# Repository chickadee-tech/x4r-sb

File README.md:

# Chickadee Tech X4R-SB Cradle Polystack Mod #
This mod cradles an X4R-SB to add it to the Polystack. It supports both the Serial RX and telemetry connections.

## Documentation ##
See the [wiki](https://github.com/chickadee-tech/x4r-sb/wiki) for documentation.

## Polystack ##
This **mod** board is part of the Polystack platform for modular microcontrol systems. More information on the platform can be found at [polystack.org](http://polystack.org).

## Support ##
If you need support with a board you own or have development questions please email support@chickadee.tech or check [chickadee.tech/support](https://chickadee.tech/support) for other ways to get support.

## Contributing ##
Please note that this project is released with a [Contributor Code of Conduct](CODE_OF_CONDUCT.md). By participating in this project you agree to abide by its terms.

### Setup ###
Components and footprints for PCB parts are not included in this repository. Instead, checkout the [chickadee-tech/kicad-libs](https://github.com/chickadee-tech/kicad-libs) repository in the same directory that this repository is checked out in. All part definitions should be relative so that they will load correctly.

### Pull requests ###
For fixes please submit a pull request to the original repository. After the pull request is merged, check the [Chickadee Tech Active Contributor Discount (ACD)](https://chickadee.tech/active-contributor) to see if you are eligible for a discount code to use on your next purchase.

### Derivatives ###
If developing your own version of the X4R-SB board please remove all Chickadee Tech trademarks and follow the [CC-BY license](LICENSE). While not required, please consider open sourcing your modifications so others can learn from your improvements. If you do email support@chickadee.tech and we may choose to add your project to the ACD.

You may also license the Polystack logo for free by emailing support@chickadee.tech. We'll ask for your gerbers to ensure the design complies with specifications laid out [here](https://github.com/chickadee-tech/polystack/wiki) and provide written permission to use the trademark after compliance has been demonstrated.

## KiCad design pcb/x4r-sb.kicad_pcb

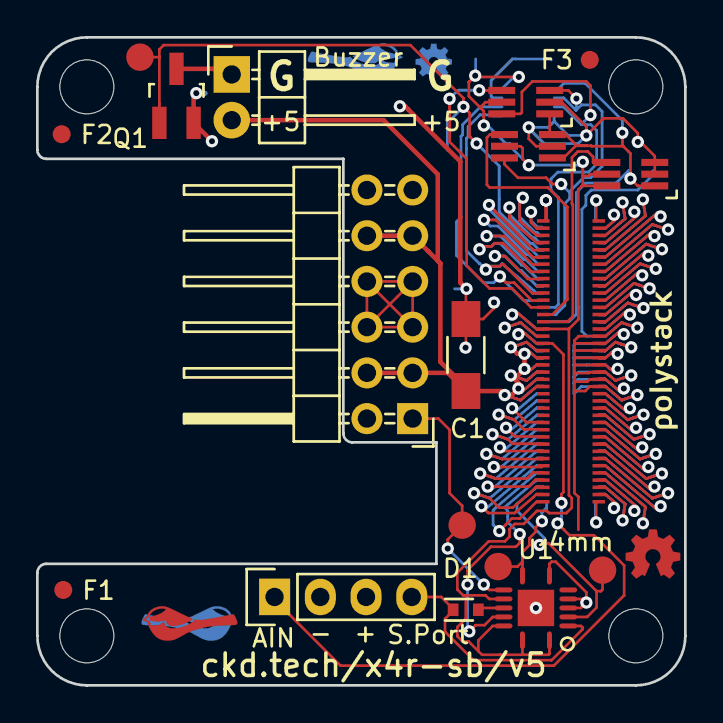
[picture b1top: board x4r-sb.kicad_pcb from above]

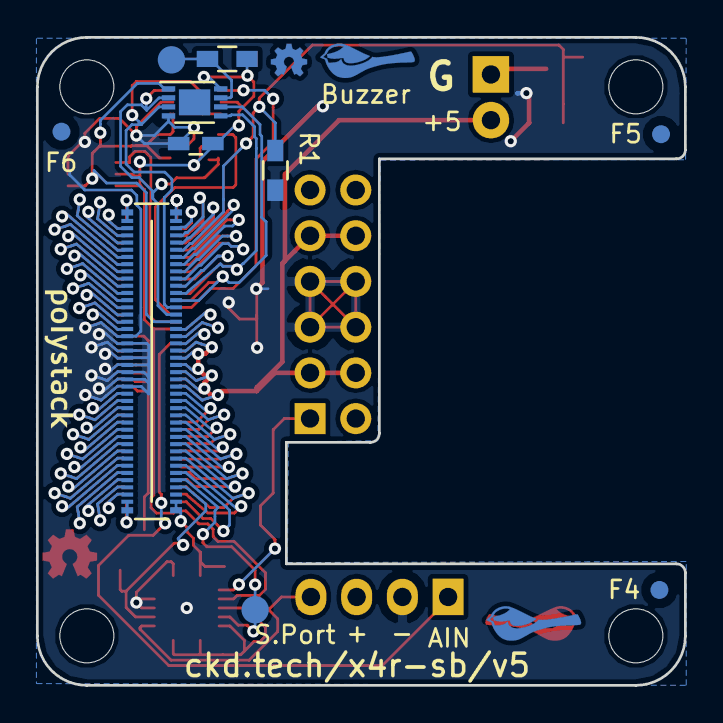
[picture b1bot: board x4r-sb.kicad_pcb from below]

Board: 2 copper layers, 36.0 x 36.0 mm, 30 parts (11 on the bottom side), 75 nets.

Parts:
C1: 10uF; C_1206_HandSoldering
D1: D_Schottky_Small; SOD-523
F1, F2, F3, F4, F5, F6: 1mm; Fiducial
P1: CONN_01X04; Pin_Header_Straight_1x04
P2: CONN_02X06; Pin_Header_Angled_2x06
P3: CONN_01X02; Pin_Header_Angled_1x02
P5, P7, P8, P9, P10: CONN_01X01; Measurement_Point_Round-SMD-Pad_Small
PORT_ANDOR1: SN74LVC1G0832; SC-70-6_Handsoldering
PORT_C1: 0.1uF; C_0603_HandSoldering
PORT_IC1: AT24CS02-MAHM; DFN-8-1EP_3x2mm_Pitch0.5mm
PORT_IN1: CKD_SANDWICH; DF40-80pin-Header
PORT_INV1: SN74LVC1G58; SC-70-6_Handsoldering
PORT_OUT1: CKD_SANDWICH; DF40-3-4mm-80pin-Receptacle
PORT_P1: CONN_01X01; Measurement_Point_Round-SMD-Pad_Small
PORT_R1: 10k; R_0603_HandSoldering
PORT_XOR1: SN74LVC1G58; SC-70-6_Handsoldering
Q1: Q_NMOS_GSD; SOT-23_Handsoldering
R1: 10k; R_0603_HandSoldering
U1: 74LS86; QFN-14-3.5x3.5mm
svg2mod, svg2mod#2: G***; polystack-bold-0.4

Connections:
+3V3: PORT_ANDOR1.5, PORT_C1.1, PORT_IC1.8, PORT_IN1.16, PORT_INV1.5, PORT_INV1.6, PORT_OUT1.16, PORT_R1.2, PORT_XOR1.5, U1.1, U1.10, U1.13, U1.14
+5V: C1.1, P2.3, P2.4, P2.9, P2.10, P3.2, PORT_IN1.19, PORT_IN1.20, PORT_IN1.21, PORT_IN1.22, PORT_IN1.23, PORT_IN1.24, PORT_OUT1.19, PORT_OUT1.20, PORT_OUT1.21, PORT_OUT1.22, PORT_OUT1.23, PORT_OUT1.24
/ExpansionPort/3V3_0.3A_E: PORT_IN1.17, PORT_OUT1.17
/ExpansionPort/ADC1: PORT_IN1.49, PORT_OUT1.49
/ExpansionPort/ADC2: PORT_IN1.50, PORT_OUT1.50
/ExpansionPort/BATT_DIV: P1.1, PORT_IN1.18, PORT_OUT1.18
/ExpansionPort/BOOT: PORT_IN1.65, PORT_OUT1.65
/ExpansionPort/CAN_HI: PORT_IN1.67, PORT_OUT1.67
/ExpansionPort/CAN_LO: PORT_IN1.68, PORT_OUT1.68
/ExpansionPort/GPIO1: P10.1, PORT_IN1.5, Q1.1, R1.1
/ExpansionPort/GPIO2: PORT_IN1.6, PORT_OUT1.5
/ExpansionPort/GPIO3: PORT_IN1.7, PORT_OUT1.6
/ExpansionPort/GPIO4: PORT_IN1.8, PORT_OUT1.7
/ExpansionPort/GPIO5: PORT_IN1.9, PORT_OUT1.8
/ExpansionPort/GPIO6: PORT_IN1.10, PORT_OUT1.9
/ExpansionPort/HEIGHT_1: PORT_ANDOR1.1, PORT_IC1.1, PORT_IN1.15, PORT_INV1.1, PORT_XOR1.1, PORT_XOR1.3
/ExpansionPort/HEIGHT_2: PORT_ANDOR1.3, PORT_IC1.2, PORT_IN1.14, PORT_XOR1.6
/ExpansionPort/HEIGHT_4: PORT_ANDOR1.6, PORT_IC1.3, PORT_IN1.13
/ExpansionPort/NEW_HEIGHT_1: PORT_INV1.4, PORT_OUT1.15
/ExpansionPort/NEW_HEIGHT_2: PORT_OUT1.14, PORT_XOR1.4
/ExpansionPort/NEW_HEIGHT_4: PORT_ANDOR1.4, PORT_OUT1.13
/ExpansionPort/RESET: PORT_IN1.66, PORT_OUT1.66
/ExpansionPort/SDMMC1_CK: PORT_IN1.55, PORT_OUT1.55
/ExpansionPort/SDMMC1_CMD: PORT_IN1.56, PORT_OUT1.56
/ExpansionPort/SDMMC1_D0: PORT_IN1.51, PORT_OUT1.51
/ExpansionPort/SDMMC1_D1: PORT_IN1.52, PORT_OUT1.52
/ExpansionPort/SDMMC1_D2: PORT_IN1.53, PORT_OUT1.53
/ExpansionPort/SDMMC1_D3: PORT_IN1.54, PORT_OUT1.54
/ExpansionPort/SPI1_MISO: PORT_IN1.79, PORT_OUT1.79
/ExpansionPort/SPI1_MOSI: PORT_IN1.80, PORT_OUT1.80
/ExpansionPort/SPI1_NSS: PORT_IN1.77, PORT_OUT1.77
/ExpansionPort/SPI1_SCK: PORT_IN1.78, PORT_OUT1.78
/ExpansionPort/SPI2_MISO: PORT_IN1.75, PORT_OUT1.75
/ExpansionPort/SPI2_MOSI: PORT_IN1.76, PORT_OUT1.76
/ExpansionPort/SPI2_NSS: PORT_IN1.73, PORT_OUT1.73
/ExpansionPort/SPI2_SCK: PORT_IN1.74, PORT_OUT1.74
/ExpansionPort/SPI3_MISO: PORT_IN1.71, PORT_OUT1.71
/ExpansionPort/SPI3_MOSI: PORT_IN1.72, PORT_OUT1.72
/ExpansionPort/SPI3_NSS: PORT_IN1.69, PORT_OUT1.69
/ExpansionPort/SPI3_SCK: PORT_IN1.70, PORT_OUT1.70
/ExpansionPort/TIM1: PORT_IN1.1, PORT_OUT1.1
/ExpansionPort/TIM2: PORT_IN1.2, PORT_OUT1.2
/ExpansionPort/TIM3: PORT_IN1.3, PORT_OUT1.3
/ExpansionPort/TIM4: PORT_IN1.4, PORT_OUT1.4
/ExpansionPort/TIMG1_CH1: PORT_IN1.41, PORT_OUT1.41
/ExpansionPort/TIMG1_CH2: PORT_IN1.42, PORT_OUT1.42
/ExpansionPort/TIMG1_CH3: PORT_IN1.43, PORT_OUT1.43
/ExpansionPort/TIMG1_CH4: PORT_IN1.44, PORT_OUT1.44
/ExpansionPort/TIMG2_CH1: PORT_IN1.45, PORT_OUT1.45
/ExpansionPort/TIMG2_CH2: PORT_IN1.46, PORT_OUT1.46
/ExpansionPort/TIMG2_CH3: PORT_IN1.47, PORT_OUT1.47
/ExpansionPort/TIMG2_CH4: PORT_IN1.48, PORT_OUT1.48
/ExpansionPort/UART1_RX: P7.1, PORT_IN1.40, U1.8
/ExpansionPort/UART2_RX: P8.1, PORT_IN1.38, U1.3
/ExpansionPort/UART2_TX: P9.1, PORT_IN1.37, U1.12
/ExpansionPort/UART3_RX: PORT_IN1.36, PORT_OUT1.40
/ExpansionPort/UART3_TX: PORT_IN1.35, PORT_OUT1.39
/ExpansionPort/UART4_RX: PORT_IN1.34, PORT_OUT1.38
/ExpansionPort/UART4_TX: PORT_IN1.33, PORT_OUT1.37
/ExpansionPort/UART5_RX: PORT_IN1.32, PORT_OUT1.36
/ExpansionPort/UART5_TX: PORT_IN1.31, PORT_OUT1.35
/ExpansionPort/UART6_RX: PORT_IN1.30, PORT_OUT1.34
/ExpansionPort/UART6_TX: PORT_IN1.29, PORT_OUT1.33
/ExpansionPort/UART7_RX: PORT_IN1.28, PORT_OUT1.32
/ExpansionPort/UART7_TX: PORT_IN1.27, PORT_OUT1.31
/ExpansionPort/UART8_RX: PORT_IN1.26, PORT_OUT1.30
/ExpansionPort/UART8_TX: PORT_IN1.25, PORT_OUT1.29
/ExpansionPort/i2c_SCL: PORT_IC1.6, PORT_IN1.12, PORT_OUT1.12
/ExpansionPort/i2c_SDA: PORT_IC1.5, PORT_IN1.11, PORT_OUT1.11
/S.Port: D1.1, P1.4, U1.2
/nRC_RX: P2.1, P5.1, U1.9
GND: C1.2, P1.2, P2.5, P2.6, P2.7, P2.8, PORT_ANDOR1.2, PORT_C1.2, PORT_IC1.4, PORT_IN1.57, PORT_IN1.58, PORT_IN1.59, PORT_IN1.60, PORT_IN1.61, PORT_IN1.62, PORT_IN1.63, PORT_IN1.64, PORT_INV1.2, PORT_INV1.3, PORT_OUT1.57, PORT_OUT1.58, PORT_OUT1.59, PORT_OUT1.60, PORT_OUT1.61, PORT_OUT1.62, PORT_OUT1.63, PORT_OUT1.64, PORT_XOR1.2, Q1.2, R1.2, U1.4, U1.5, U1.7
unnamed: D1.2, U1.11
unnamed: P3.1, Q1.3
unnamed: PORT_IC1.7, PORT_P1.1, PORT_R1.1

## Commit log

2016-01-26 Cradles an x4r and connects telemtry and S.Bus automatically. Also has a buzzer connection.
2016-02-06 v2 of x4r cradle that switchs to an XOR inverter gate. Also shifts the buzzer pins a little.
2016-03-05 X4R-SB v2 which corrects the inversion circuit.
2016-04-07 Unknown changes to x4r
2016-04-11 Correct X4R schema label and add PDFs.
2016-04-13 Rebrand everything to Polystack and increment versions.
2016-04-16 Final gerbers for test manufacturing run.
2016-06-07 Update polystack logo to bold variant and bump version number.
2016-07-07 Add license information to many files. PCB design files are CC-BY and code is MIT license.
2016-07-07 Add back .gitignore after repo split.
2016-07-07 Convert to relative component and footprint paths.

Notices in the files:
pcb/x4r-sb.kicad_pcb:
Copyright 2016 Chickadee Tech LLC,
This work is licensed under the Creative Commons Attribution 4.0 International License.
To view a copy of this license, visit http://creativecommons.org/licenses/by/4.0
or send a letter to Creative Commons, PO Box 1866, Mountain View, CA 94042, USA.
